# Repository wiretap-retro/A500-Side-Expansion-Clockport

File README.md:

# A500 Side Expansion Clockport
A simple clockport adapter for the A500 side expansion slot.

## Info
Designed for my Amiga 500 tower. Might fit inside a the factory A500 case. Functionally tested by Fletch with an A314cp. Will not work with a A1200 RTC since the appropriate clock signals aren't present on the A500 side expansion bus. Please solder bridge INT6_EN, unless you have a specific use case where it is not necessary.

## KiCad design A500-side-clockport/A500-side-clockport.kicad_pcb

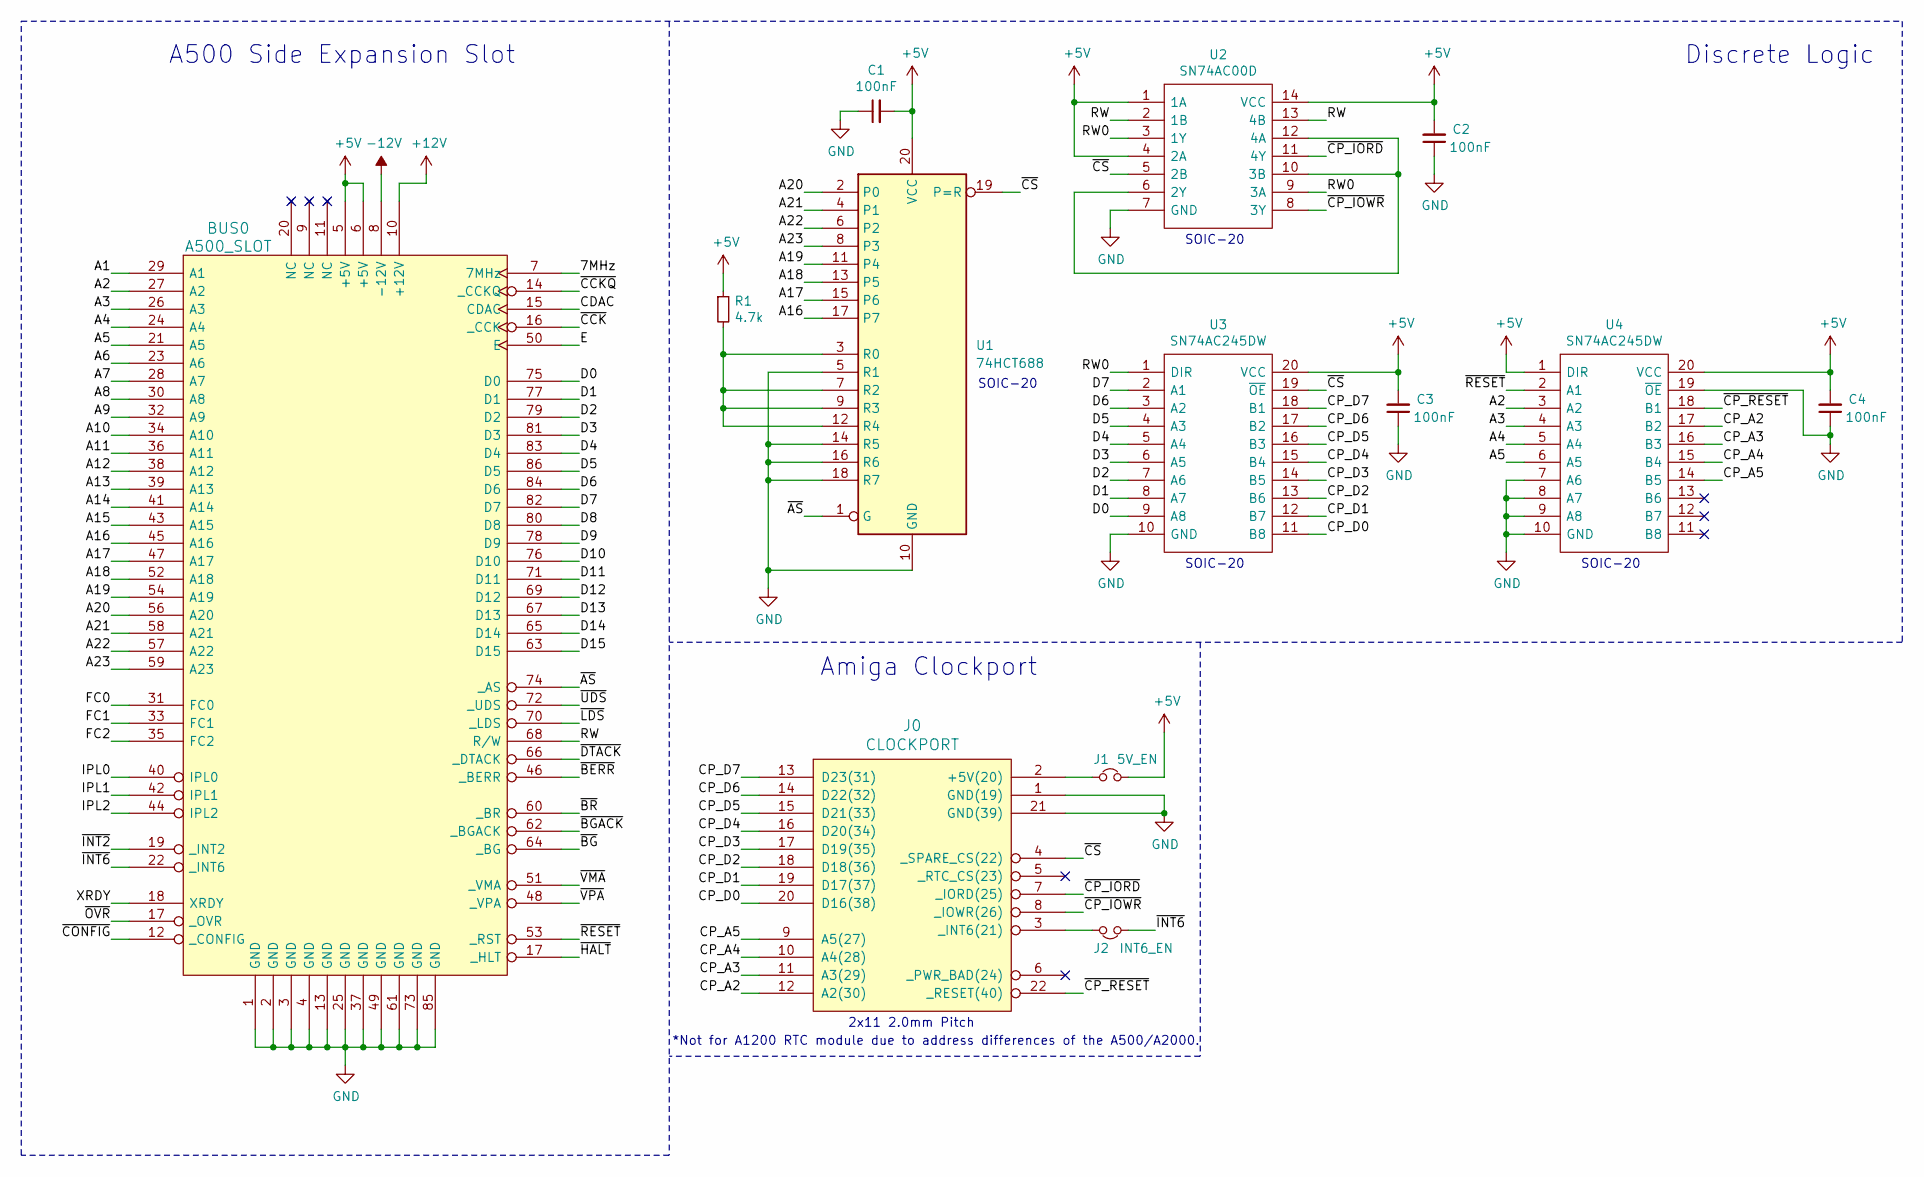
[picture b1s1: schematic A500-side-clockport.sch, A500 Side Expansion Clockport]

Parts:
BUS0: A500_SLOT; TE_1-5530843-0
C1, C2, C3, C4: 100nF; C_0805_2012Metric_Pad1.15x1.40mm_HandSolder
J0: CLOCKPORT; PinHeader_2x11_P2.00mm_Vertical
J1: 5V_EN; SolderJumper-2_P1.3mm_Open_RoundedPad1.0x1.5mm
J2: INT6_EN; SolderJumper-2_P1.3mm_Open_RoundedPad1.0x1.5mm
R1: 4.7k; R_0805_2012Metric_Pad1.15x1.40mm_HandSolder
U1: 74HCT688; SOIC-20W_7.5x12.8mm_P1.27mm
U2: SN74AC00D; SOIC127P600X175-14N; Mouser Part Number 595-SN74AC00D
U3, U4: SN74AC245DW; SOIC127P1030X265-20N; Mouser Part Number 595-SN74AC245DW

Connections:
+5V: BUS0.5 (+5V), BUS0.6 (+5V), C1.2, C2.2, C3.2, C4.2, J1.2, R1.1, U1.20 (VCC), U2.1 (1A), U2.4 (2A), U2.14 (VCC), U3.20 (VCC), U4.1 (DIR), U4.20 (VCC)
+12V: BUS0.10 (+12V)
-12V: BUS0.8 (-12V)
/7MHz: BUS0.7 (7MHz)
/A1: BUS0.29 (A1)
/A2: BUS0.27 (A2), U4.3 (A2)
/A3: BUS0.26 (A3), U4.4 (A3)
/A4: BUS0.24 (A4), U4.5 (A4)
/A5: BUS0.21 (A5), U4.6 (A5)
/A6: BUS0.23 (A6)
/A7: BUS0.28 (A7)
/A8: BUS0.30 (A8)
/A9: BUS0.32 (A9)
/A10: BUS0.34 (A10)
/A11: BUS0.36 (A11)
/A12: BUS0.38 (A12)
/A13: BUS0.39 (A13)
/A14: BUS0.41 (A14)
/A15: BUS0.43 (A15)
/A16: BUS0.45 (A16), U1.17 (P7)
/A17: BUS0.47 (A17), U1.15 (P6)
/A18: BUS0.52 (A18), U1.13 (P5)
/A19: BUS0.54 (A19), U1.11 (P4)
/A20: BUS0.56 (A20), U1.2 (P0)
/A21: BUS0.58 (A21), U1.4 (P1)
/A22: BUS0.57 (A22), U1.6 (P2)
/A23: BUS0.59 (A23), U1.8 (P3)
/CDAC: BUS0.15 (CDAC)
/CP_A2: J0.12 (A2(30)), U4.17 (B2)
/CP_A3: J0.11 (A3(29)), U4.16 (B3)
/CP_A4: J0.10 (A4(28)), U4.15 (B4)
/CP_A5: J0.9 (A5(27)), U4.14 (B5)
/CP_D0: J0.20 (D16(38)), U3.11 (B8)
/CP_D1: J0.19 (D17(37)), U3.12 (B7)
/CP_D2: J0.18 (D18(36)), U3.13 (B6)
/CP_D3: J0.17 (D19(35)), U3.14 (B5)
/CP_D4: J0.16 (D20(34)), U3.15 (B4)
/CP_D5: J0.15 (D21(33)), U3.16 (B3)
/CP_D6: J0.14 (D22(32)), U3.17 (B2)
/CP_D7: J0.13 (D23(31)), U3.18 (B1)
/D0: BUS0.75 (D0), U3.9 (A8)
/D1: BUS0.77 (D1), U3.8 (A7)
/D2: BUS0.79 (D2), U3.7 (A6)
/D3: BUS0.81 (D3), U3.6 (A5)
/D4: BUS0.83 (D4), U3.5 (A4)
/D5: BUS0.86 (D5), U3.4 (A3)
/D6: BUS0.84 (D6), U3.3 (A2)
/D7: BUS0.82 (D7), U3.2 (A1)
/D8: BUS0.80 (D8)
/D9: BUS0.78 (D9)
/D10: BUS0.76 (D10)
/D11: BUS0.71 (D11)
/D12: BUS0.69 (D12)
/D13: BUS0.67 (D13)
/D14: BUS0.65 (D14)
/D15: BUS0.63 (D15)
/E: BUS0.50 (E)
/FC0: BUS0.31 (FC0)
/FC1: BUS0.33 (FC1)
/FC2: BUS0.35 (FC2)
/IPL0: BUS0.40 (IPL0)
/IPL1: BUS0.42 (IPL1)
/IPL2: BUS0.44 (IPL2)
/RW: BUS0.68 (R/W), U2.2 (1B), U2.13 (4B)
/RW0: U2.3 (1Y), U2.9 (3A), U3.1 (DIR)
/XRDY: BUS0.18 (XRDY)
/~AS: BUS0.74 (_AS), U1.1 (G)
/~BERR: BUS0.46 (_BERR)
/~BG: BUS0.64 (_BG)
/~BGACK: BUS0.62 (_BGACK)
/~BR: BUS0.60 (_BR)
/~CCK: BUS0.16 (_CCK)
/~CCKQ: BUS0.14 (_CCKQ)
/~CONFIG: BUS0.12 (_CONFIG)
/~CP_IORD: J0.7 (_IORD(25)), U2.11 (4Y)
/~CP_IOWR: J0.8 (_IOWR(26)), U2.8 (3Y)
/~CP_RESET: J0.22 (_RESET(40)), U4.18 (B1)
/~CS: J0.4 (_SPARE_CS(22)), U1.19 (P=R), U2.5 (2B), U3.19 (~OE)
/~DTACK: BUS0.66 (_DTACK)
/~INT2: BUS0.19 (_INT2)
/~INT6: BUS0.22 (_INT6), J2.1
/~LDS: BUS0.70 (_LDS)
/~RESET: BUS0.53 (_RST), U4.2 (A1)
/~UDS: BUS0.72 (_UDS)
/~VMA: BUS0.51 (_VMA)
/~VPA: BUS0.48 (_VPA)
GND: BUS0.1 (GND), BUS0.2 (GND), BUS0.3 (GND), BUS0.4 (GND), BUS0.13 (GND), BUS0.25 (GND), BUS0.37 (GND), BUS0.49 (GND), BUS0.61 (GND), BUS0.73 (GND), BUS0.85 (GND), C1.1, C2.1, C3.1, C4.1, J0.1 (GND(19)), J0.21 (GND(39)), U1.5 (R1), U1.10 (GND), U1.14 (R5), U1.16 (R6), U1.18 (R7), U2.7 (GND), U3.10 (GND), U4.7 (A6), U4.8 (A7), U4.9 (A8), U4.10 (GND), U4.19 (~OE)
unnamed: J0.2 (+5V(20)), J1.1
unnamed: J0.3 (_INT6(21)), J2.2
unnamed: R1.2, U1.3 (R0), U1.7 (R2), U1.9 (R3), U1.12 (R4)
unnamed: U2.6 (2Y), U2.10 (3B), U2.12 (4A)

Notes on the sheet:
A500 Side Expansion Slot
Amiga Clockport
SOIC-20
2x11 2.0mm Pitch
Discrete Logic
*Not for A1200 RTC module due to address differences of the A500/A2000.

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
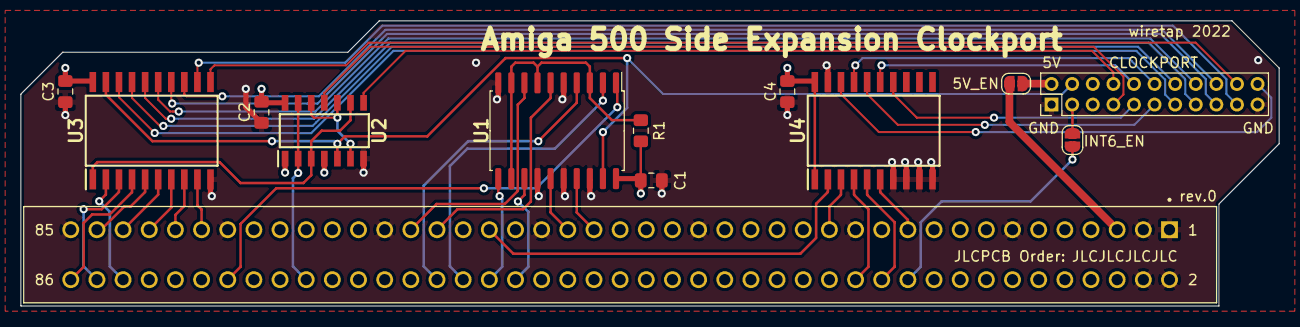
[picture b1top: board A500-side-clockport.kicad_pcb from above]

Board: 4 copper layers, 122.2 x 27.7 mm, 13 parts (0 on the bottom side), 47 nets.

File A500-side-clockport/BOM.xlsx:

Reference | Value | Footprint | Description | Manufacturer Name | Manufacturer Part Number
BUS0 | A500_SLOT | SamacSys_Parts:TE_1-5530843-0 | Amiga 500 side expansion slot edge connector | TE Connectivity | 1-5530843-0
C1 | 100nF | Capacitor_SMD:C_0805_2012Metric_Pad1.15x1.40mm_HandSolder | 0805 Capacitor
C2 | 100nF | Capacitor_SMD:C_0805_2012Metric_Pad1.15x1.40mm_HandSolder | 0805 Capacitor
C3 | 100nF | Capacitor_SMD:C_0805_2012Metric_Pad1.15x1.40mm_HandSolder | 0805 Capacitor
C4 | 100nF | Capacitor_SMD:C_0805_2012Metric_Pad1.15x1.40mm_HandSolder | 0805 Capacitor
J0 | CLOCKPORT | Connector_PinHeader_2.00mm:PinHeader_2x11_P2.00mm_Vertical | 2x11 2.0mm Pitch Pin Header
J1 | 5V_EN | Jumper:SolderJumper-2_P1.3mm_Open_RoundedPad1.0x1.5mm | Solder jumper
J2 | INT6_EN | Jumper:SolderJumper-2_P1.3mm_Open_RoundedPad1.0x1.5mm | Solder jumper
R1 | 4.7k | Resistor_SMD:R_0805_2012Metric_Pad1.15x1.40mm_HandSolder | 0805 Resistor
U1 | 74HCT688 | Package_SO:SOIC-20W_7.5x12.8mm_P1.27mm | 8-bit Identity Comparator | Texas Instruments | SN74HCT688DW
U2 | SN74AC00D | SamacSys_Parts:SOIC127P600X175-14N | Quadruple 2-Input Positive-NAND Gates | Texas Instruments | SN74AC00D
U3 | SN74AC245DW | SamacSys_Parts:SOIC127P1030X265-20N | Texas Instruments SN74AC245DW, Bus Transceiver, 8-Bit Non-Inverting CMOS, 2 6 V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 | Texas Instruments | SN74AC245DW
U4 | SN74AC245DW | SamacSys_Parts:SOIC127P1030X265-20N | Texas Instruments SN74AC245DW, Bus Transceiver, 8-Bit Non-Inverting CMOS, 2 6 V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 | Texas Instruments | SN74AC245DW
